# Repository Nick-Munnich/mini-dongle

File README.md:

This is an attempt to make as miniature of a dongle for ZMK as is realistically possible. PCB size: 20.66mmx11.3mm

By realistically, I mean to not be completely unaffordable to produce. 
It could be made smaller through the use of components on both sides and via-in-pad, but this would raise the cost by a large degree. Likewise for reducing the width of traces even further - theoretically sound and wouldn't have any issues with the current levels we are dealing with, but financially unviable.

Despite my best efforts, it turns out to be financially unviable for PCBA -- in large enough quantities it would be fine, but thanks to FCC/CE certification the amount of orders needed would be unrealistic for something like this.

However, it should be perfectly fine for someone who has a hot plate and happens to be ordering parts from a site such as digikey/mouser already. If someone has a reflow oven and wants me to design a version that has components on both sides, let me know.

Note that the PCB antenna trace width to get the correct impedence was calculated using JLCPCB's tool, so I cannot recommend ordering this from anywhere else without first redoing said calculation and adjusting the width appropriately.

Disclaimer: I am not a professional RF engineer, I merely followed the schematics on the datasheets for the components as closely as possible. I am fairly confident that it works, but there is always the chance of an error as it has not been tested.

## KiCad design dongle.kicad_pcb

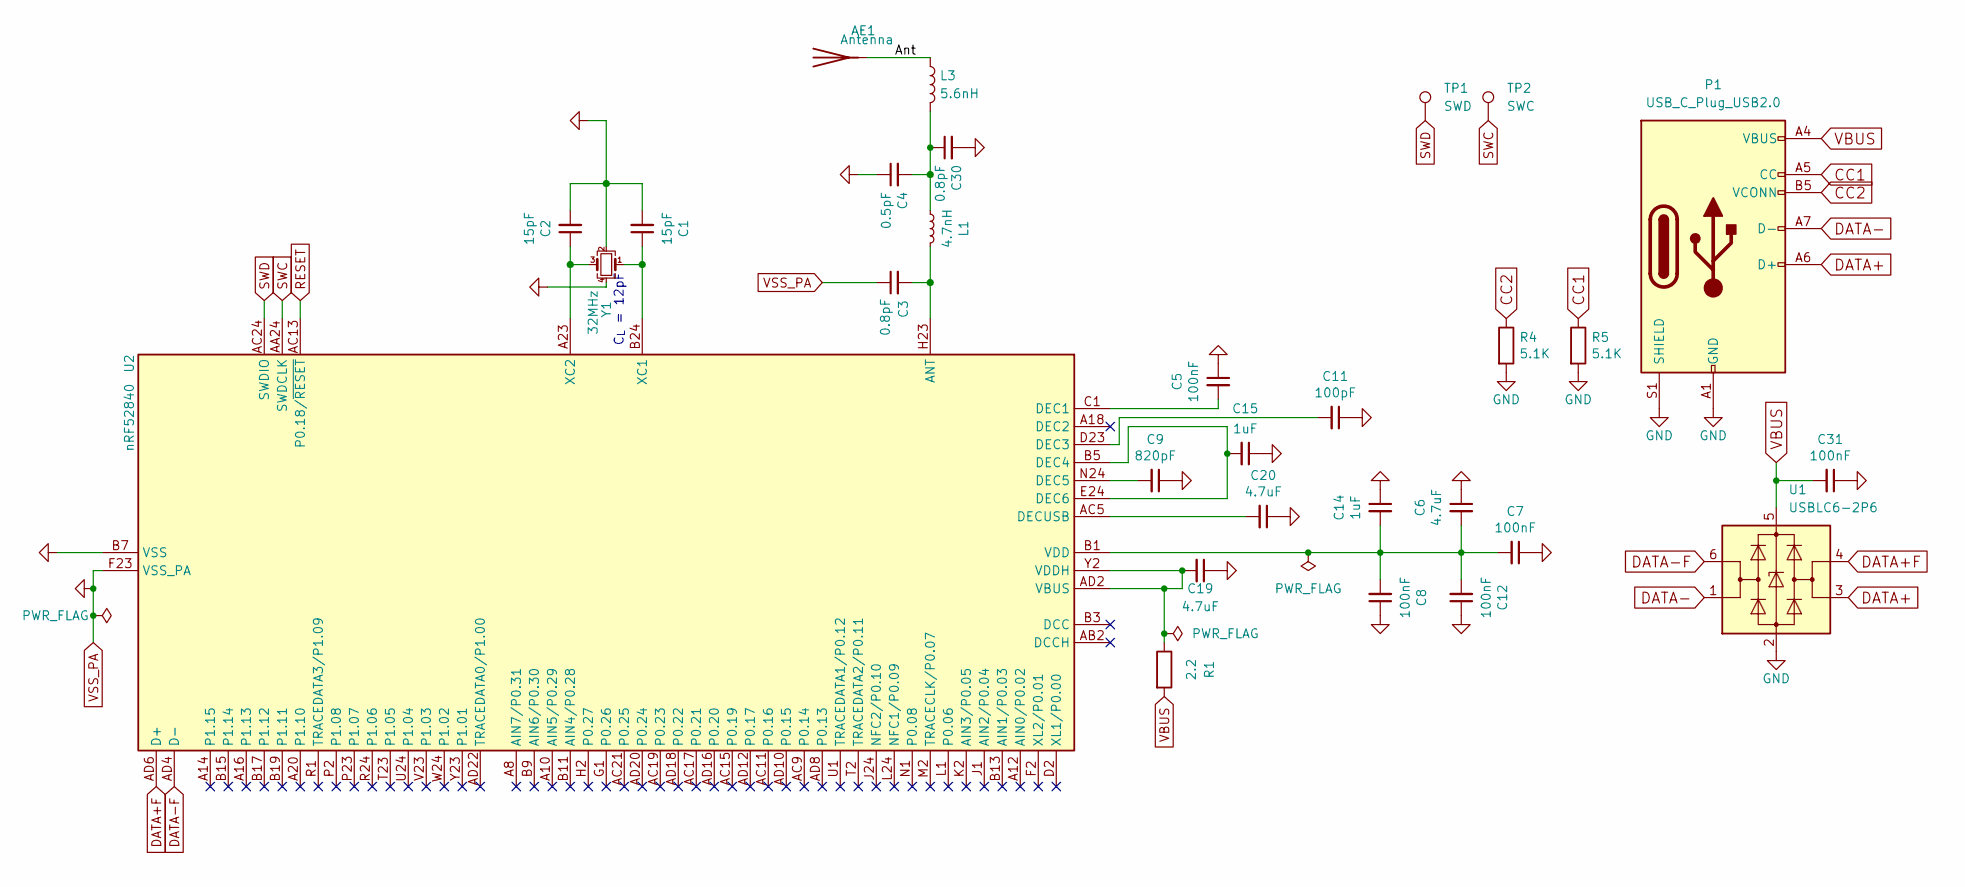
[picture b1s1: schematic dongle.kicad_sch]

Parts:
AE1: Antenna; Johanson_2450AT43F0100
C1, C2: 15pF; C_0402_1005Metric; Manufacturer Part CL05C150JB51PNC; LCSC Part C1548
C3, C30: 0.8pF; C_0402_1005Metric; Manufacturer Part CL05C010CB5NNNC; LCSC Part C1550
C4: 0.5pF; C_0402_1005Metric; Manufacturer Part CL05C010CB5NNNC; LCSC Part C1550
C5, C7, C8, C12, C31: 100nF; C_0402_1005Metric; Manufacturer Part CL05A475KP5NRNC; LCSC Part C23733
C6, C19, C20: 4.7uF; C_0402_1005Metric; Manufacturer Part CL05A475KP5NRNC; LCSC Part C23733
C9: 820pF; C_0402_1005Metric; Manufacturer Part CL05A475KP5NRNC; LCSC Part C23733
C11: 100pF; C_0402_1005Metric; Manufacturer Part CL05A475KP5NRNC; LCSC Part C23733
C14, C15: 1uF; C_0402_1005Metric; Manufacturer Part CL05A475KP5NRNC; LCSC Part C23733
L1: 4.7nH; L_0402_1005Metric; Manufacturer Part MLG1005S3N9BT000; LCSC Part C14033
L3: 5.6nH; L_0402_1005Metric
P1: USB_C_Plug_USB2.0; USB_C_Plug_Molex_105444
R1: 2.2; R_0402_1005Metric
R4, R5: 5.1K; R_0402_1005Metric
TP1: SWD; TestPoint_Pad_2.0x2.0mm
TP2: SWC; TestPoint_Pad_2.0x2.0mm
U1: USBLC6-2P6; SOT-666
U2: nRF52840; Nordic_AQFN-73-1EP_7x7mm_P0.5mm; Manufacturer Part NRF52840-QIAA-R; LCSC Part C190794
Y1: 32MHz; Crystal_SMD_2016-4Pin_2.0x1.6mm; Manufacturer Part Q22FA1280001800; LCSC Part C255896

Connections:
/Ant: AE1.1 (A), L3.1
CC1: P1.A5 (CC), R5.1
CC2: P1.B5 (VCONN), R4.1
DATA+: P1.A6 (D+), U1.3 (I/O2)
DATA+F: U1.4 (I/O2), U2.AD6 (D+)
DATA-: P1.A7 (D-), U1.1 (I/O1)
DATA-F: U1.6 (I/O1), U2.AD4 (D-)
unnamed: C6.2, C7.2, C8.2, C12.2, C14.2, U2.A22 (VDD), U2.AD14 (VDD), U2.AD23 (VDD), U2.B1 (VDD), U2.W1 (VDD)
unnamed: C4.2, C30.1, L1.1, L3.2
unnamed: C3.2, L1.2, U2.H23 (ANT)
unnamed: C5.2, U2.C1 (DEC1)
unnamed: C11.2, U2.D23 (DEC3)
unnamed: C15.2, U2.B5 (DEC4), U2.E24 (DEC6)
unnamed: C9.2, U2.N24 (DEC5)
unnamed: C20.2, U2.AC5 (DECUSB)
unnamed: C19.2, R1.1, U2.AD2 (VBUS), U2.Y2 (VDDH)
unnamed: C1.1, U2.B24 (XC1), Y1.1
unnamed: C2.1, U2.A23 (XC2), Y1.3
RESET: U2.AC13 (P0.18/~RESET)
SWC: TP2.1, U2.AA24 (SWDCLK)
SWD: TP1.1, U2.AC24 (SWDIO)
VBUS: C31.2, P1.A4 (VBUS), P1.A9 (VBUS), P1.B4 (VBUS), P1.B9 (VBUS), R1.2, U1.5 (VBUS)
VSS_PA: C1.2, C2.2, C3.1, C4.1, C5.1, C6.1, C7.1, C8.1, C9.1, C11.1, C12.1, C14.1, C15.1, C19.1, C20.1, C30.2, C31.1, P1.A1 (GND), P1.A12 (GND), P1.B1 (GND), P1.B12 (GND), P1.S1 (SHIELD), R4.2, R5.2, U1.2 (GND), U2.B7 (VSS), U2.EP (VSS), U2.F23 (VSS_PA), Y1.2, Y1.4

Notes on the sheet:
C_{L} = 12pF

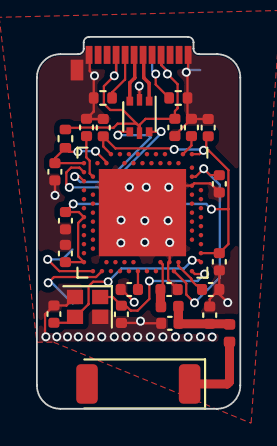
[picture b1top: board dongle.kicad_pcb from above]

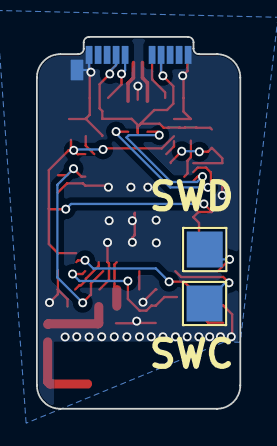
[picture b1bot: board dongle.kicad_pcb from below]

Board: 2 copper layers, 11.3 x 20.7 mm, 29 parts (2 on the bottom side), 22 nets.

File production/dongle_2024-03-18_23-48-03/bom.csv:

Designator,Footprint,Quantity,Value,LCSC Part #
"C1, C2",0402,2,15pF,C1548
C11,0402,1,100pF,C23733
"C12, C31, C5, C7, C8",0402,5,100nF,C23733
"C14, C15",0402,2,1uF,C23733
"C19, C20, C6",0402,3,4.7uF,C23733
"C3, C30",0402,2,0.8pF,C1550
C4,0402,1,0.5pF,C1550
C9,0402,1,820pF,C23733
L1,0402,1,4.7nH,C14033
L3,0402,1,5.6nH,
P1,USB_C_Plug_Molex_105444,1,USB_C_Plug_USB2.0,
R1,0402,1,2.2,
"R4, R5",0402,2,5.1K,
TP1,TestPoint_Pad_2.0x2.0mm,1,SWD,
TP2,TestPoint_Pad_2.0x2.0mm,1,SWC,
U1,SOT-666,1,USBLC6-2P6,
U2,Nordic_AQFN-73-1EP_7x7mm_P0.5mm,1,nRF52840,C190794
Y1,Crystal_SMD_2016-4Pin_2.0x1.6mm,1,32MHz,C255896

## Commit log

2024-03-18 Stuff
2024-03-19 added readme
2024-03-19 added production files
2024-03-19 forgot a silkscreen marker
2024-03-19 added image on request
